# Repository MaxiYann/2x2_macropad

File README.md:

# 2x2_macropad
KiCAD files for my first kb PCB, a 2 by 2 macropad

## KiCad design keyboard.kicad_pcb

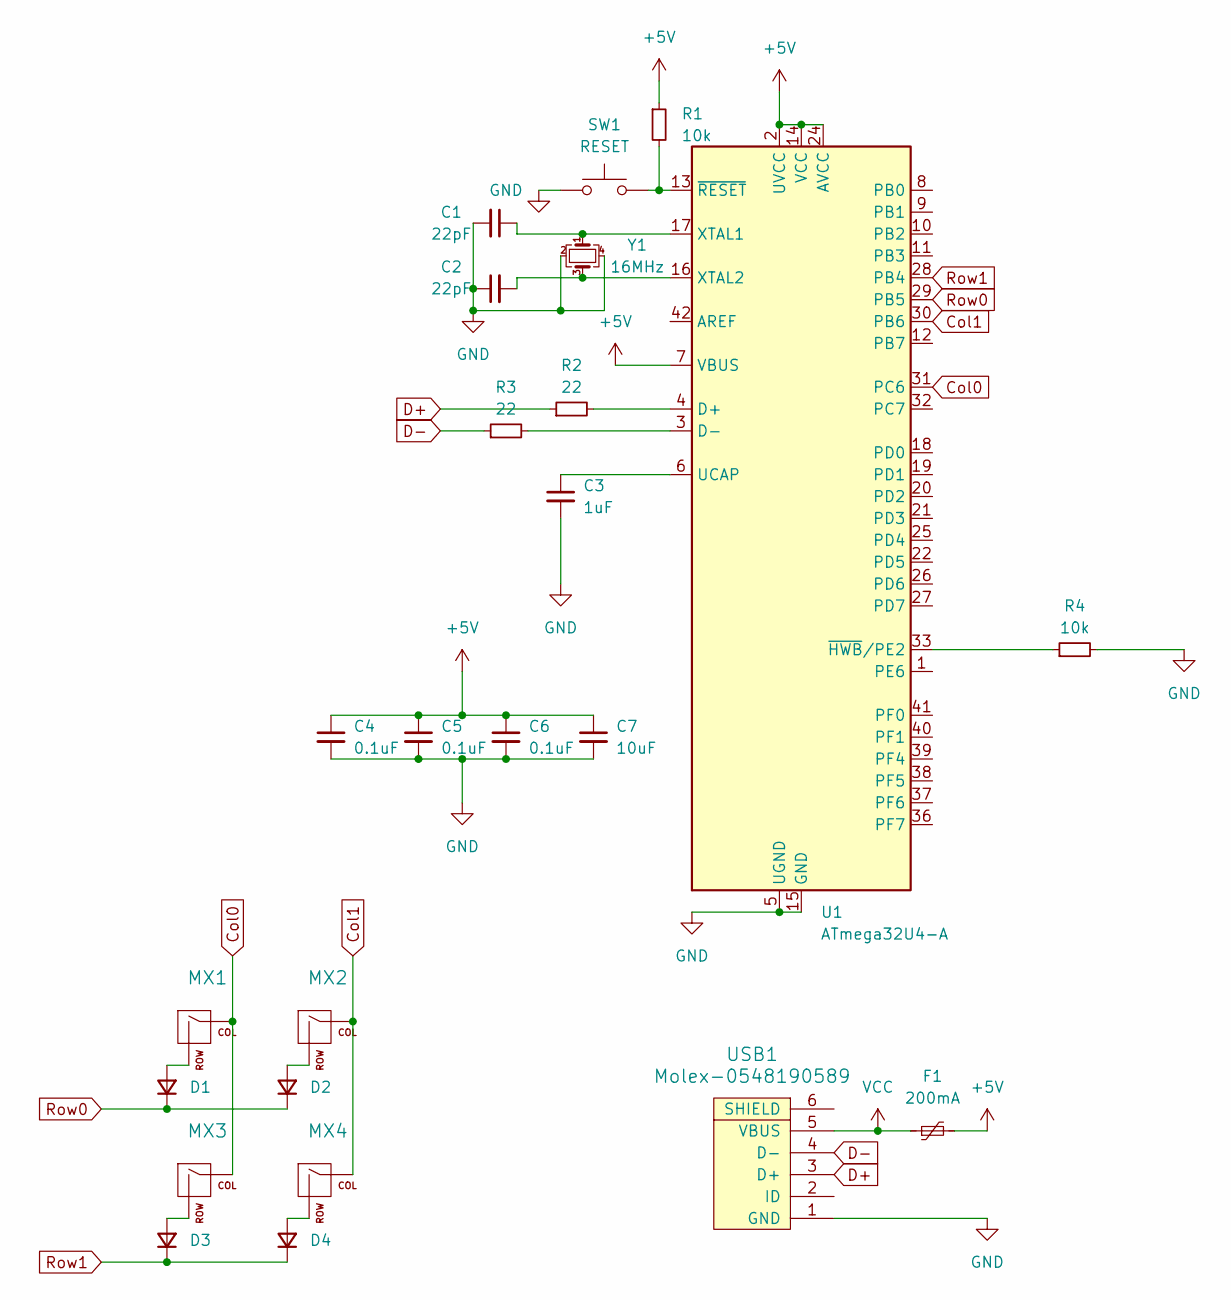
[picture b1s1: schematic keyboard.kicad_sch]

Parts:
C1, C2: 22pF; C_0805_2012Metric
C3: 1uF; C_0805_2012Metric
C4, C5, C6: 0.1uF; C_0805_2012Metric
C7: 10uF; C_0805_2012Metric
D1, D2, D3, D4: D_SOD-123
F1: 200mA; Fuse_1206_3216Metric
MX1, MX2, MX3, MX4: MX-1U-NoLED
R1, R4: 10k; R_0805_2012Metric
R2, R3: 22; R_0805_2012Metric
SW1: RESET; SKQG-1155865
U1: ATmega32U4-A; TQFP-44_10x10mm_P0.8mm
USB1: Molex-0548190589
Y1: 16MHz; Crystal_SMD_3225-4Pin_3.2x2.5mm

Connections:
+5V: C4.1, C5.1, C6.1, C7.1, F1.2, R1.1, U1.2 (UVCC), U1.7 (VBUS), U1.14 (VCC), U1.24 (AVCC), U1.34 (VCC), U1.44 (AVCC)
Col0: MX1.1 (COL), MX3.1 (COL), U1.31 (PC6)
Col1: MX2.1 (COL), MX4.1 (COL), U1.30 (PB6)
D+: R2.1, USB1.3 (D+)
D-: R3.1, USB1.4 (D-)
GND: C1.2, C2.1, C3.2, C4.2, C5.2, C6.2, C7.2, R4.2, SW1.1, U1.5 (UGND), U1.15 (GND), U1.23 (GND), U1.35 (GND), U1.43 (GND), USB1.1 (GND), Y1.2, Y1.4
unnamed: D1.2 (A), MX1.2 (ROW)
unnamed: D2.2 (A), MX2.2 (ROW)
unnamed: D3.2 (A), MX3.2 (ROW)
unnamed: D4.2 (A), MX4.2 (ROW)
unnamed: R2.2, U1.4 (D+)
unnamed: R3.2, U1.3 (D-)
unnamed: C3.1, U1.6 (UCAP)
unnamed: C1.1, U1.17 (XTAL1), Y1.1
unnamed: C2.2, U1.16 (XTAL2), Y1.3
unnamed: R4.1, U1.33 (~HWB/PE2)
unnamed: R1.2, SW1.2, U1.13 (~RESET)
Row0: D1.1 (K), D2.1 (K), U1.29 (PB5)
Row1: D3.1 (K), D4.1 (K), U1.28 (PB4)
VCC: F1.1, USB1.5 (VBUS)

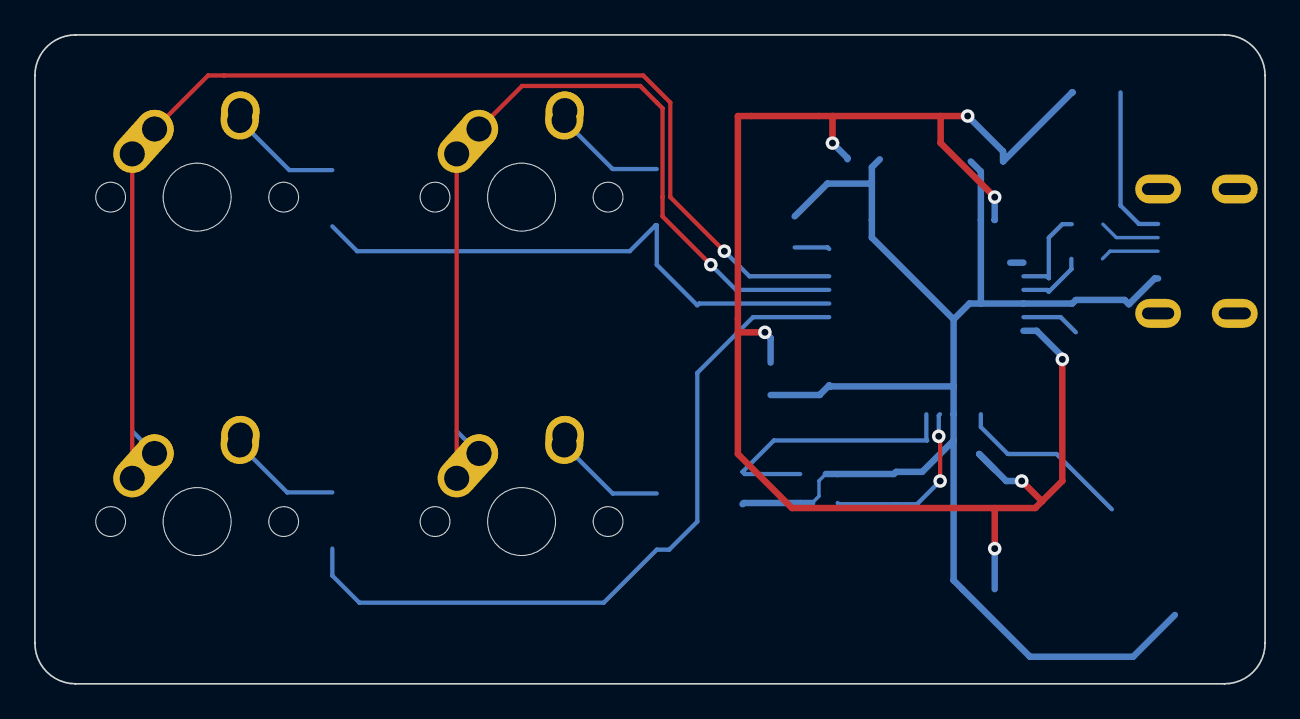
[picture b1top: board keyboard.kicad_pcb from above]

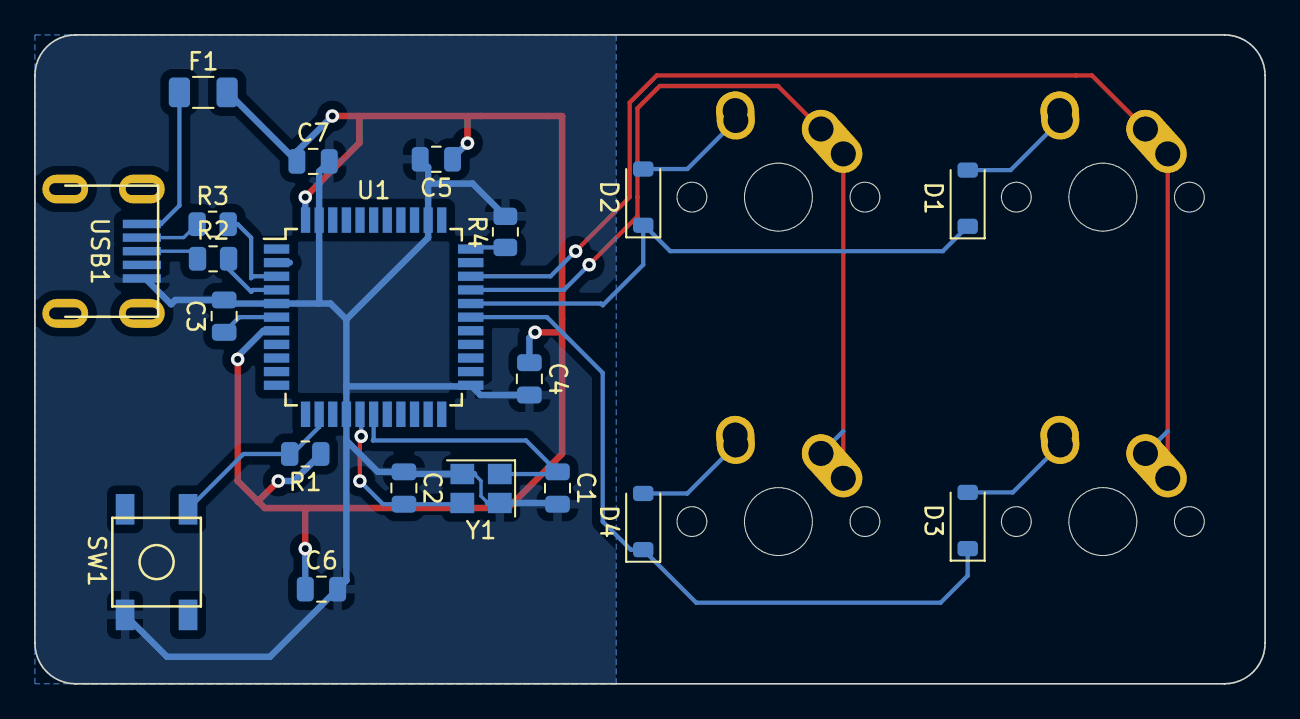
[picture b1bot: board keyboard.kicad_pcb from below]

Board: 2 copper layers, 72.2 x 38.1 mm, 24 parts (20 on the bottom side), 20 nets.

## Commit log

2023-10-09 Inital commit
2023-10-09 Added submodules
2023-10-09 Added libraries
2023-10-09 Schematic done
2023-10-09 PCB done
2023-10-09 Fixed errors + gerber files
2023-10-09 Moved gerber files
2023-10-09 Created gerber.zip archive
